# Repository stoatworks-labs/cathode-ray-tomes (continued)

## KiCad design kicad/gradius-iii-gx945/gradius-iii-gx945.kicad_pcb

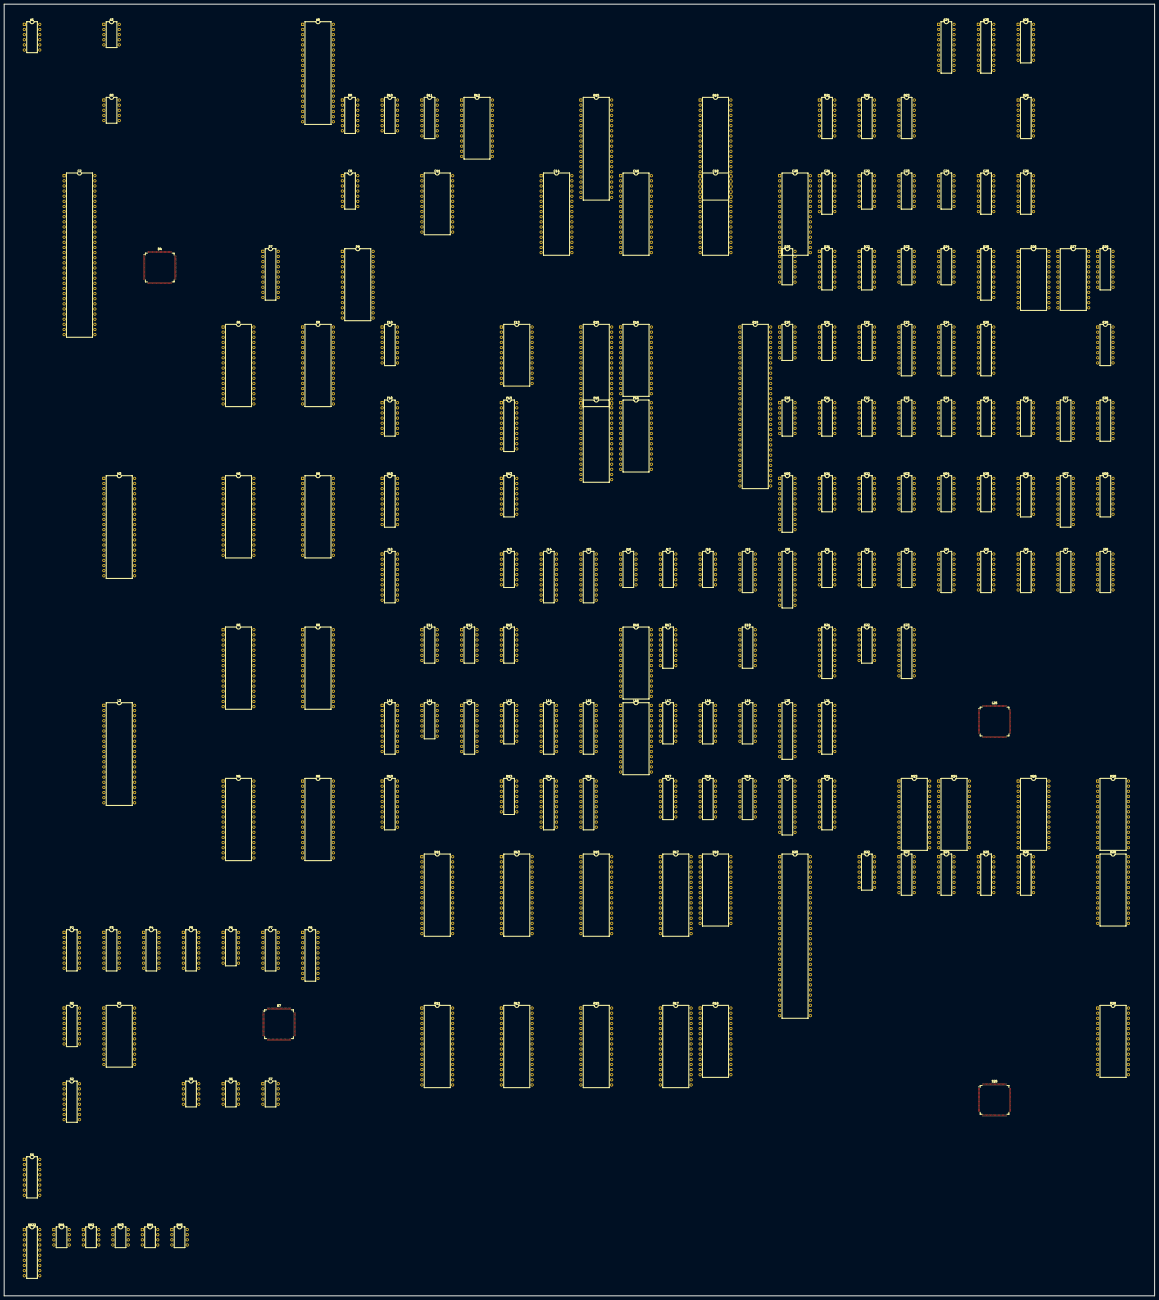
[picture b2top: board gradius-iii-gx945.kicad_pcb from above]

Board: 2 copper layers, 570.1 x 640.1 mm, 180 parts (0 on the bottom side), 849 nets, no tracks yet.

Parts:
A1: MB3731; DIP-12_W7.62mm
A3: 007340; DIP-10_W7.62mm
A8: Z80; DIP-40_W15.24mm
A24: 74LS244; DIP-20_W7.62mm
A25: 74LS273; DIP-20_W7.62mm
A26: 74LS257; DIP-16_W7.62mm
B3: 007340; DIP-10_W7.62mm
B9: 74LS04; DIP-14_W7.62mm
B10: UPC324; DIP-14_W7.62mm
B11: YM3012; DIP-16_W7.62mm
B12: 051550; DIP-24_W15.24mm
B15, B18: 23C4100; DIP-40_W15.24mm
B21: 74LS157; DIP-16_W7.62mm
B22, B23: 74LS138; DIP-16_W7.62mm
B26: 74LS257; DIP-16_W7.62mm
C2: 007232; DIP-64_W15.24mm
C9: UPC324; DIP-14_W7.62mm
C11: YM2151; DIP-24_W15.24mm
C14, C16, C18, C20: 27C1000; DIP-32_W15.24mm
C21: 74LS174; DIP-16_W7.62mm
C22, C23, C24: 74LS07; DIP-14_W7.62mm
C25, C26: 74LS253; DIP-16_W7.62mm
D4: 051937; TQFP-120_14x14mm_P0.4mm
D7, D25: 74LS273; DIP-20_W7.62mm
D9: 27C512; DIP-28_W15.24mm
D20: 74LS04; DIP-14_W7.62mm
D21: 74LS174; DIP-16_W7.62mm
D22: 74LS139; DIP-16_W7.62mm
D23: 74LS74; DIP-14_W7.62mm
D24: 74LS07; DIP-14_W7.62mm
D26, D27: SRAM2K8B; DIP-24_W15.24mm
D28: 74LS253; DIP-16_W7.62mm
E6, E8: 27C1000; DIP-32_W15.24mm
E10: 74LS138; DIP-16_W7.62mm
E13: SRAM2K8B; DIP-24_W15.24mm
E15: 27C1000-255; DIP-32_W15.24mm
E16: SRAM8K8B; DIP-28_W15.24mm
E19: MC68000; DIP-64_W15.24mm
E20: 74LS32; DIP-14_W7.62mm
E21: 74LS04; DIP-14_W7.62mm
E22: 74LS74; DIP-14_W7.62mm
E23, E24: 74LS245; DIP-20_W7.62mm
E25: 74LS273; DIP-20_W7.62mm
E28: 74LS253; DIP-16_W7.62mm
F10: 74LS08; DIP-14_W7.62mm
F13: 74LS374; DIP-20_W7.62mm
F15: 27C1000-255; DIP-32_W15.24mm
F16: SRAM8K8B; DIP-28_W15.24mm
F20, F23, F26: 74LS32; DIP-14_W7.62mm
F21: 74LS04; DIP-14_W7.62mm
F22, F24: 74LS74; DIP-14_W7.62mm
F25: 74LS07; DIP-14_W7.62mm
F27, F28: 74LS157; DIP-16_W7.62mm
H3: 23C4100; DIP-40_W15.24mm
H6, H8: 27C1000; DIP-32_W15.24mm
H10: 74LS244; DIP-20_W7.62mm
H13: 74LS139; DIP-16_W7.62mm
H20: 007644; DIP-22_W7.62mm
H21: 74LS74; DIP-14_W7.62mm
H22: 74LS08; DIP-14_W7.62mm
H23: 74LS10; DIP-14_W7.62mm
H24: 74LS32; DIP-14_W7.62mm
H25: 74LS04; DIP-14_W7.62mm
H26: 74LS174; DIP-16_W7.62mm
H27: 74LS273; DIP-20_W7.62mm
H28: 74LS157; DIP-16_W7.62mm
J10, J14, J15: 74LS244; DIP-20_W7.62mm
J13: 74LS08; DIP-14_W7.62mm
J16: 74LS00; DIP-14_W7.62mm
J17: 74LS32; DIP-14_W7.62mm
J18, J21, J22: 74LS74; DIP-14_W7.62mm
J19: 74LS157; DIP-16_W7.62mm
J20: 007644; DIP-22_W7.62mm
J23: 74LS02; DIP-14_W7.62mm
J24, J25, J26, J27: 74LS153; DIP-16_W7.62mm
J28: PROM256W4B; DIP-16_W7.62mm
K6, K8: 27C1000; DIP-32_W15.24mm
K11: 74LS04; DIP-14_W7.62mm
K12: 74LS74; DIP-14_W7.62mm
K13: 74LS08; DIP-14_W7.62mm
K16: SRAM8K8B; DIP-28_W15.24mm
K17, K19: 74LS157; DIP-16_W7.62mm
K21: 74LS245; DIP-20_W7.62mm
K22: 74LS07; DIP-14_W7.62mm
K23: 74LS244; DIP-20_W7.62mm
KK22: 74LS245; DIP-20_W7.62mm
L3: 23C4100; DIP-40_W15.24mm
L10, L12: 74LS244; DIP-20_W7.62mm
L11: 74LS74; DIP-14_W7.62mm
L13: 74LS138; DIP-16_W7.62mm
L14, L15, L21: 74LS245; DIP-20_W7.62mm
L16: SRAM8K8B; DIP-28_W15.24mm
L17, L18, L19: 74LS157; DIP-16_W7.62mm
L20: 007644; DIP-22_W7.62mm
L25: 051962; TQFP-120_14x14mm_P0.4mm
M6, M8: 27C1000; DIP-32_W15.24mm
M10: 74LS244; DIP-20_W7.62mm
M13: 74LS04; DIP-14_W7.62mm
M14, M15, M21: 74LS245; DIP-20_W7.62mm
M17, M18, M19: 74LS157; DIP-16_W7.62mm
M20: 007644; DIP-22_W7.62mm
M23, M24, M26, M28: SRAM32K8B; DIP-28_W15.24mm
N11, N13, N15, N17: 27C1000-255; DIP-32_W15.24mm
N18, N28: SRAM8K8B; DIP-28_W15.24mm
N20: MC68000; DIP-64_W15.24mm
N22: 74LS00; DIP-14_W7.62mm
N23, N24, N25, N26: 74LS157; DIP-16_W7.62mm
P2, P3, P4, P5, P7: 74LS157; DIP-16_W7.62mm
P6: 74LS32; DIP-14_W7.62mm
P8: 74LS244; DIP-20_W7.62mm
R2: 74LS174; DIP-16_W7.62mm
R3: SRAM2K8B; DIP-24_W15.24mm
R7: 051960; TQFP-120_14x14mm_P0.4mm
R11, R13, R15, R17: 27C1000-255; DIP-32_W15.24mm
R18, R28: SRAM8K8B; DIP-28_W15.24mm
RN1, RN2, RN3, RN4, RN5: 005273; DIP-8_W7.62mm
S2: 74LS367; DIP-16_W7.62mm
S5, S6, S7: 052535; DIP-10_W7.62mm
S25: 052109; TQFP-120_14x14mm_P0.4mm
U1: 74LS157; DIP-16_W7.62mm

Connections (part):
+12V: A1.11, B10.4, B12.19, C9.4
/10M: E19.15, J14.3
/10M': J14.7, J21.3, J21.11
/10M'': J14.12, N20.15
/CLK24M: D4.2, M13.10, R7.2
/CLK24M': L25.90, M13.8, S25.65
/CLK24M'': J18.3, M13.2
/CLK24M''': E21.5, F22.11, F24.3, H25.13, M13.4
/CPU Master/COIN1: B12.15, E25.2
/CPU Master/COIN2: B12.16, E25.5
/CPU Master/MA1: A24.2, E15.12, E16.10, E19.29, F15.12, F16.10, L17.2
/CPU Master/MA2: A24.4, E15.11, E16.9, E19.30, F15.11, F16.9, L17.5
/CPU Master/MA3: A24.6, E15.10, E16.8, E19.31, F15.10, F16.8, L17.11
/CPU Master/MA4: A24.8, E15.9, E16.7, E19.32, F15.9, F16.7, L17.14
/CPU Master/MA5: A24.11, E15.8, E16.6, E19.33, F15.8, F16.6, M17.2
/CPU Master/MA6: A24.13, E15.7, E16.5, E19.34, F15.7, F16.5, M17.5
/CPU Master/MA7: A24.15, E15.6, E16.4, E19.35, F15.6, F16.4, M17.11
/CPU Master/MA8: A24.17, E15.5, E16.3, E19.36, F15.5, F16.3, M17.14
/CPU Master/MA9: E15.27, E16.25, E19.37, F15.27, F16.25, K17.2, K23.2
/CPU Master/MA10: E15.26, E16.24, E19.38, F15.26, F16.24, K17.5, K23.4
/CPU Master/MA11: E15.23, E16.21, E19.39, F15.23, F16.21, K17.11, K23.6
/CPU Master/MA12: E15.25, E16.23, E19.40, F15.25, F16.23, K17.14, K23.8
/CPU Master/MA13: E15.4, E16.2, E19.41, F15.4, F16.2, J19.2, K23.11
/CPU Master/MA14: E15.28, E19.42, F15.28, K23.13
/CPU Master/MA15: B22.1, E15.29, E19.43, F15.29, K23.15
/CPU Master/MA16: B22.2, E15.3, E19.44, F15.3, K23.17
/CPU Master/MA17: B22.3, E15.2, E19.45, F15.2
/CPU Master/MA18: B23.1, E19.46
/CPU Master/MA19: B23.2, E19.47
/CPU Master/MA20: B23.3, E19.48, F23.2
/CPU Master/MA23: B23.4, E19.52, J16.1
/CPU Master/MAS: E21.12, H22.9, J16.2
/CPU Master/MD0: E19.5, F15.13, F16.11, L15.18
/CPU Master/MD1: E19.4, F15.14, F16.12, L15.17
/CPU Master/MD2: E19.3, F15.15, F16.13, L15.16
/CPU Master/MD3: E19.2, F15.17, F16.15, L15.15
/CPU Master/MD4: E19.1, F15.18, F16.16, L15.14
/CPU Master/MD5: E19.64, F15.19, F16.17, L15.13
/CPU Master/MD6: E19.63, F15.20, F16.18, L15.12
/CPU Master/MD7: E19.62, F15.21, F16.19, L15.11
/CPU Master/MD8: E15.13, E16.11, E19.61, E25.3, M15.18
/CPU Master/MD9: E15.14, E16.12, E19.60, E25.4, M15.17
/CPU Master/MD10: E15.15, E16.13, E19.59, E25.7, M15.16
/CPU Master/MD11: E15.17, E16.15, E19.58, E25.8, M15.15
/CPU Master/MD12: E15.18, E16.16, E19.57, E25.13, M15.14
/CPU Master/MD13: E15.19, E16.17, E19.56, E25.14, M15.13
/CPU Master/MD14: E15.20, E16.18, E19.55, E25.17, M15.12
/CPU Master/MD15: E15.21, E16.19, E19.54, E25.18, M15.11
/CPU Master/MIRQEN: E25.16, H21.4
/CPU Master/MR~W: D20.5, E19.9, E20.4, E20.13, J15.2
/CPU Master/MR~W': F23.5, J15.18, L15.1, M15.1
/CPU Master/MVBIRQEN0: E25.12, J22.4
/CPU Master/MVBIRQEN1: E25.15, H21.10
/CPU Master/M~RW: D20.6, E16.22, F16.22, F26.9, U1.10
/CPU Master/PRIO: E25.6, J28.15
/CPU Master/~AFR: B12.1, B22.11
/CPU Master/~CABINPUTS: B22.14, C25.1, C25.15, C26.1, C26.15, D28.1, D28.15, E28.1, E28.15
/CPU Master/~DIPSW: A26.15, B22.13, B26.15
/CPU Master/~MAS: B23.5, E19.6, E21.13, J15.4
/CPU Master/~MCHRAMW: B23.9, F20.12, H22.1
/CPU Master/~MDTACK: D24.8, D24.10, D24.12, E19.10
/CPU Master/~MHALT: E19.17, F25.8
/CPU Master/~MLDS: E19.8, E20.12
/CPU Master/~MLWR: E20.11, F16.27, F26.2, F26.5, U1.3
/CPU Master/~MRAM: B23.14, E16.20, F16.20
/CPU Master/~MRESET: E19.18, F25.10
/CPU Master/~MROM: B23.15, E15.24, F15.24
/CPU Master/~MUDS: E19.7, E20.5
/CPU Master/~MUWR: E16.27, E20.1, E20.6, F26.12, U1.6
/CPU Master/~PALRAM: E21.4, E23.19, E24.19, F26.1, F26.13, F27.1, F28.1, H28.1
/CPU Master/~SCPURST: D24.3, E25.9, F25.5, K13.2, R2.1
/CPU Master/~SIRQ: B22.12, J22.11
/CPU Master/~SNDDATA: B22.10, F13.11
/CPU Master/~SNDIRQ: B22.9, E22.11
/CPU Master/~VBLK: J22.3, K11.1, K11.3, R7.3
/CPU Slave/SA1: L12.2, L17.3, N11.12, N13.12, N15.12, N17.12, N18.10, N20.29, R11.12, R13.12, R15.12, R17.12, R18.10
/CPU Slave/SA2: L12.4, L17.6, N11.11, N13.11, N15.11, N17.11, N18.9, N20.30, R11.11, R13.11, R15.11, R17.11, R18.9
/CPU Slave/SA3: L12.6, L17.10, N11.10, N13.10, N15.10, N17.10, N18.8, N20.31, R11.10, R13.10, R15.10, R17.10, R18.8
/CPU Slave/SA4: L12.8, L17.13, N11.9, N13.9, N15.9, N17.9, N18.7, N20.32, R11.9, R13.9, R15.9, R17.9, R18.7
/CPU Slave/SA5: L12.11, M17.3, N11.8, N13.8, N15.8, N17.8, N18.6, N20.33, R11.8, R13.8, R15.8, R17.8, R18.6
/CPU Slave/SA6: L12.13, M17.6, N11.7, N13.7, N15.7, N17.7, N18.5, N20.34, R11.7, R13.7, R15.7, R17.7, R18.5
/CPU Slave/SA7: L12.15, M17.10, N11.6, N13.6, N15.6, N17.6, N18.4, N20.35, R11.6, R13.6, R15.6, R17.6, R18.4
/CPU Slave/SA8: L12.17, M17.13, N11.5, N13.5, N15.5, N17.5, N18.3, N20.36, R11.5, R13.5, R15.5, R17.5, R18.3
/CPU Slave/SA9: K17.3, N11.27, N13.27, N15.27, N17.27, N18.25, N20.37, P8.2, R11.27, R13.27, R15.27, R17.27, R18.25
/CPU Slave/SA10: K17.6, N11.26, N13.26, N15.26, N17.26, N18.24, N20.38, P8.4, R11.26, R13.26, R15.26, R17.26, R18.24
/CPU Slave/SA11: K17.10, N11.23, N13.23, N15.23, N17.23, N18.21, N20.39, P8.6, R11.23, R13.23, R15.23, R17.23, R18.21
/CPU Slave/SA12: K17.13, N11.25, N13.25, N15.25, N17.25, N18.23, N20.40, P8.8, R11.25, R13.25, R15.25, R17.25, R18.23
/CPU Slave/SA13: J19.3, N11.4, N13.4, N15.4, N17.4, N18.2, N20.41, P8.11, R11.4, R13.4, R15.4, R17.4, R18.2
/CPU Slave/SA14: N11.28, N13.28, N15.28, N17.28, N20.42, P8.13, R11.28, R13.28, R15.28, R17.28
/CPU Slave/SA15: N11.29, N13.29, N15.29, N17.29, N20.43, P8.15, R11.29, R13.29, R15.29, R17.29
/CPU Slave/SA16: N11.3, N13.3, N15.3, N17.3, N20.44, P8.17, R11.3, R13.3, R15.3, R17.3
/CPU Slave/SA17: N11.2, N13.2, N15.2, N17.2, N20.45, R11.2, R13.2, R15.2, R17.2, S2.2
/CPU Slave/SA18: H13.2, L13.1, N20.46, S2.4
/CPU Slave/SA19: H13.3, L13.2, N20.47, S2.6
/CPU Slave/SA20: L13.3, N20.48, S2.10
/CPU Slave/SA21: E21.11, F20.1, L13.4, N20.50
/CPU Slave/SA22: F21.13, F23.12, L13.5, N20.51
/CPU Slave/SA23: J16.5, N20.52
/CPU Slave/SAS: J16.4, J21.4, J21.10, K11.6, K12.4, K13.1, L13.6
/CPU Slave/SIRQEN: J22.10, R2.7
/CPU Slave/SR~W: F21.11, H24.9, H24.12, J14.6, N20.9
/CPU Slave/SVBIRQEN0: L11.4, R2.2
/CPU Slave/SVBIRQEN1: L11.10, R2.5
/CPU Slave/S~RW: D4.7, F20.10, F21.10, N18.22, R7.12, R18.22, U1.11
/CPU Slave/~MIRQ: H21.3, K22.13, L13.9
/CPU Slave/~OBJCS: D4.8, K12.5, K22.11, R7.13
/CPU Slave/~OBJROMRD: F20.6, J13.10, P2.1, P3.1, P4.1, P5.1, P6.1, P6.4, P6.9, P6.12, P7.1
/CPU Slave/~SAS': J14.9, K11.5
/CPU Slave/~SAS: F20.5, H24.2, J14.11, N20.6
/CPU Slave/~SCHRAMW: H13.6, J13.1, J17.1
/CPU Slave/~SDTACK: F25.2, F25.12, K22.2, K22.4, K22.6, K22.8, K22.10, K22.12, N20.10
/CPU Slave/~SHALT: F25.6, N20.17
/CPU Slave/~SIRQEN: K22.3, L13.10, R2.9
/CPU Slave/~SLDS: H24.13, N20.8
/CPU Slave/~SLWR: H24.11, J17.4, N18.27, U1.2
/CPU Slave/~SRAM: K22.5, L13.11, N18.20, R18.20
/CPU Slave/~SRESET: D24.4, N20.18
/CPU Slave/~SROM0: K22.9, L13.15, N17.24, R17.24
/CPU Slave/~SROM1: K13.13, L13.14, N15.24, R15.24
/CPU Slave/~SROM2: K13.9, L13.13, N11.24, R11.24
/CPU Slave/~SROM3: K13.10, L13.12, N13.24, R13.24
/CPU Slave/~SUDS: H24.10, N20.7
/CPU Slave/~SUWR: E20.9, H24.8, R18.27, U1.5
/CPU Slave/~VBLK: D4.29, K11.11, L11.3
/Color Mixer/B0: A25.3, D27.9, E24.18
/Color Mixer/B1: A25.4, D27.10, E24.17
/Color Mixer/B2: A25.7, D27.11, E24.16
/Color Mixer/B3: A25.8, D27.13, E24.15
/Color Mixer/B4: A25.13, D27.14, E24.14
/Color Mixer/B'0: A25.2, D24.5
/Color Mixer/B'1: A25.5, C23.11
/Color Mixer/B'2: A25.6, C24.9
/Color Mixer/B'3: A25.9, F25.3
/Color Mixer/B'4: A25.12, C23.3
/Color Mixer/CD0: H27.3, J25.7
/Color Mixer/CD1: H27.4, J25.9
/Color Mixer/CD2: H27.7, J27.7
/Color Mixer/CD3: H27.8, J27.9
/Color Mixer/CD4: H27.13, J26.7
/Color Mixer/CD5: H27.14, J26.9
/Color Mixer/CD6: H27.17, J24.7
/Color Mixer/CD7: H27.18, J24.9
/Color Mixer/CD8: H26.3, J24.14, J25.14, J26.14, J27.14, J28.12
/Color Mixer/CD9: H26.4, J24.2, J25.2, J26.2, J27.2, J28.11
/Color Mixer/CD'0: F28.3, H27.2
/Color Mixer/CD'1: F28.6, H27.5
/Color Mixer/CD'2: F28.10, H27.6
/Color Mixer/CD'3: F28.13, H27.9
/Color Mixer/CD'4: F27.3, H27.12
/Color Mixer/CD'5: F27.6, H27.15
/Color Mixer/CD'6: F27.10, H27.16
/Color Mixer/CD'7: F27.13, H27.19
/Color Mixer/CD'8: H26.2, H28.3
/Color Mixer/CD'9: H26.5, H28.6
/Color Mixer/CD''0: D26.4, D27.2, F28.4
/Color Mixer/CD''1: D26.2, D27.23, F28.7
/Color Mixer/CD''2: D26.1, D27.1, F28.9
/Color Mixer/CD''3: D26.8, D27.5, F28.12
/Color Mixer/CD''4: D26.7, D27.4, F27.4
/Color Mixer/CD''5: D26.5, D27.3, F27.7
/Color Mixer/CD''6: D26.22, D27.7, F27.9
/Color Mixer/CD''7: D26.23, D27.8, F27.12
/Color Mixer/CD''8: D26.3, D27.22, H28.4
/Color Mixer/CD''9: D26.6, D27.19, H28.7
/Color Mixer/CD''10: D26.19, D27.6, H28.9
/Color Mixer/CLK6M: A25.11, D4.116, D25.11, H26.9, H27.11
/Color Mixer/FX0: J25.6, L25.59
/Color Mixer/FX1: J25.10, L25.60
/Color Mixer/FX2: J27.6, L25.62
/Color Mixer/FX3: J27.10, L25.63
/Color Mixer/FX4: J26.6, L25.64
/Color Mixer/FX5: J26.10, L25.65
/Color Mixer/FX6: J24.6, L25.66
/Color Mixer/G0: A25.14, D27.15, E24.13
/Color Mixer/G1: A25.17, D27.16, E24.12
/Color Mixer/G2: A25.18, D27.17, E24.11
/Color Mixer/G3: D25.3, D26.9, E23.18
/Color Mixer/G4: D25.4, D26.10, E23.17
/Color Mixer/G'0: A25.15, C23.1
/Color Mixer/G'1: A25.16, C23.5
/Color Mixer/G'2: A25.19, C24.5
/Color Mixer/G'3: C23.13, D25.2
/Color Mixer/G'4: C24.13, D25.5
/Color Mixer/OB0: D4.35, J27.11
/Color Mixer/OB1: D4.36, J27.5
/Color Mixer/OB2: D4.37, J25.11
/Color Mixer/OB3: D4.38, J25.5
/Color Mixer/OB5: D4.40, J26.5
/Color Mixer/OB6: D4.41, J26.11
/Color Mixer/OB7: D4.42, J24.5
/Color Mixer/OB8: D4.43, J24.11
/Color Mixer/OB9: D4.46, J28.3
/Color Mixer/OB10: D4.47, J28.2
/Color Mixer/PAL: D26.17, E23.11
/Color Mixer/R0: D25.7, D26.11, E23.16
/Color Mixer/R1: D25.8, D26.13, E23.15
/Color Mixer/R2: D25.13, D26.14, E23.14
/Color Mixer/R3: D25.14, D26.15, E23.13
/Color Mixer/R4: D25.17, D26.16, E23.12
/Color Mixer/R'0: C24.3, D25.6
/Color Mixer/R'1: C24.11, D25.9
/Color Mixer/R'2: C24.1, D25.12
/Color Mixer/R'3: C23.9, D25.15
/Color Mixer/R'4: D24.1, D25.16
/Color Mixer/SHADOW': D4.32, J28.1
/Color Mixer/VA0: J25.4, L25.46
/Color Mixer/VA1: J25.12, L25.47
/Color Mixer/VA2: J27.4, L25.48
/Color Mixer/VA3: J27.12, L25.49
/Color Mixer/VA4: J26.4, L25.50
/Color Mixer/VA5: J26.12, L25.51
/Color Mixer/VA6: J24.4, L25.52
/Color Mixer/VB0: J25.3, L25.30
/Color Mixer/VB1: J25.13, L25.32
/Color Mixer/VB2: J27.3, L25.33
/Color Mixer/VB3: J27.13, L25.34
/Color Mixer/VB4: J26.3, L25.35
/Color Mixer/VB5: J26.13, L25.36
/Color Mixer/VB6: J24.3, L25.37
/Color Mixer/~CBLK'': C22.9, C22.11, C22.13, D25.19
/Color Mixer/~CBLK': D25.18, H26.15
/Color Mixer/~CBLK: D4.28, H26.14
/Color Mixer/~CDEN': H26.7, H28.10
/Color Mixer/~CDEN: H26.6, J24.1, J24.15, J25.1, J25.15, J26.1, J26.15, J27.1, J27.15, J28.9
/Color Mixer/~FX: J28.5, L25.68
/Color Mixer/~OBJ: D4.33, J28.6
/Color Mixer/~PALOE: D26.20, D27.20, H28.12
/Color Mixer/~SHADOW': C22.1, C22.3, C22.5, H26.12
/Color Mixer/~SHADOW: H26.11, J28.10
/Color Mixer/~VA: J28.7, L25.58
/Color Mixer/~VB: J28.4, L25.43
/IO/INPUT0: D28.5, RN1.7
/IO/INPUT1: E28.13, RN1.5
/IO/INPUT2: E28.12, RN1.3
/IO/INPUT3: E28.11, RN1.1
/IO/INPUT4: D28.12, RN2.7
/IO/INPUT5: D28.11, RN2.5
/IO/INPUT7: D28.4, RN2.1
/IO/INPUT8: C25.4, RN3.7
/IO/INPUT9: C25.5, RN3.5
/IO/INPUT10: C26.12, RN3.3
/IO/INPUT11: C26.11, RN3.1
/IO/INPUT12: C26.3, RN4.7
/IO/INPUT13: C26.4, RN4.5
/IO/INPUT14: C26.5, RN4.3
/IO/INPUT15: D28.13, RN4.1
/IO/INPUT16: C25.13, RN5.7
/IO/INPUT17: C25.12, RN5.5
/IO/INPUT18: C25.11, RN5.3
/IO/INPUT19: C25.3, RN5.1
/IO/~COINCOUNTER1: B12.22, B12.23
/IO/~COINCOUNTER2: B12.20, B12.21
/MBA1: A24.18, A26.1, B26.1, F28.2, H25.1, K19.3
/MBA2: A24.16, F28.5, H25.3, K19.6
/MBA3: A24.14, F28.11, K19.10
/MBA4: A24.12, F28.14, K19.13
/MBA5: A24.9, F27.2, M19.3
/MBA6: A24.7, F27.5, M19.6
/MBA7: A24.5, F27.11, M19.10
/MBA8: A24.3, F27.14, M19.13
/MBA9: H28.2, K23.18, M18.3
/MBA10: H28.5, K23.16, M18.6
/MBA11: H28.11, K23.14, M18.10
/MBA12: K23.12, M18.13
/MBA13: K23.9, L19.3
/MBA14: K23.7, L19.6
/MBA15: K23.5, L19.10
/MBA16: K23.3, L19.13
/MD0: A26.4, C25.9, E24.2, L20.13
/MD1: A26.7, C25.7, E24.3, L20.14
/MD2: A26.9, C26.9, E24.4, L20.15
/MD3: A26.12, C26.7, E24.5, L20.16
/MD4: B26.4, D28.9, E24.6, L20.17
/MD5: B26.7, D28.7, E24.7, L20.18
/MD6: B26.9, E24.8, E28.9, L20.19
/MD7: B26.12, E24.9, E28.7, L20.20
/MD8: E23.2, F13.3, H20.13
/MD9: E23.3, F13.4, H20.14
/MD10: E23.4, F13.7, H20.15
/MD11: E23.5, F13.8, H20.16
/MD12: E23.6, F13.13, H20.17
/MD13: E23.7, F13.14, H20.18
/MD14: E23.8, F13.17, H20.19
/MD15: E23.9, F13.18, H20.20
/Misc/SR~W': J14.14, J17.9, L14.1, M14.1
/Misc/~CSYNC: D4.25, J14.2
/Misc/~RESET': J14.5, J18.1, J18.2
/Misc/~RESET: B12.10, J14.15
/Misc/~VSYNC: D4.26, J14.4
/Object Layer/A0: E6.12, E8.12, H3.9, H6.12, H8.12, K6.12, K8.12, L3.9, M6.12, M8.12, P7.4
/Object Layer/A1: E6.11, E8.11, H3.8, H6.11, H8.11, K6.11, K8.11, L3.8, M6.11, M8.11, P7.7
/Object Layer/A2: E6.10, E8.10, H3.7, H6.10, H8.10, K6.10, K8.10, L3.7, M6.10, M8.10, P7.9
/Object Layer/A3: E6.9, E8.9, H3.6, H6.9, H8.9, K6.9, K8.9, L3.6, M6.9, M8.9, P7.12
/Object Layer/A4: E6.8, E8.8, H3.5, H6.8, H8.8, K6.8, K8.8, L3.5, M6.8, M8.8, P5.4
/Object Layer/A5: E6.7, E8.7, H3.4, H6.7, H8.7, K6.7, K8.7, L3.4, M6.7, M8.7, P5.7
/Object Layer/A6: E6.6, E8.6, H3.3, H6.6, H8.6, K6.6, K8.6, L3.3, M6.6, M8.6, P5.9
/Object Layer/A7: E6.5, E8.5, H3.2, H6.5, H8.5, K6.5, K8.5, L3.2, M6.5, M8.5, P5.12
/Object Layer/A8: E6.27, E8.27, H3.40, H6.27, H8.27, K6.27, K8.27, L3.40, M6.27, M8.27, P4.4
/Object Layer/A9: E6.26, E8.26, H3.39, H6.26, H8.26, K6.26, K8.26, L3.39, M6.26, M8.26, P4.7
/Object Layer/A10: E6.23, E8.23, H3.38, H6.23, H8.23, K6.23, K8.23, L3.38, M6.23, M8.23, P4.9
/Object Layer/A11: E6.25, E8.25, H3.37, H6.25, H8.25, K6.25, K8.25, L3.37, M6.25, M8.25, P4.12
/Object Layer/A12: E6.4, E8.4, H3.36, H6.4, H8.4, K6.4, K8.4, L3.36, M6.4, M8.4, P3.4
/Object Layer/A13: E6.28, E8.28, H3.35, H6.28, H8.28, K6.28, K8.28, L3.35, M6.28, M8.28, P3.7
/Object Layer/A14: E6.29, E8.29, H3.34, H6.29, H8.29, K6.29, K8.29, L3.34, M6.29, M8.29, P3.9
/Object Layer/A15: E6.3, E8.3, H3.33, H6.3, H8.3, K6.3, K8.3, L3.33, M6.3, M8.3, P3.12
/Object Layer/A16: E6.2, E8.2, H3.32, H6.2, H8.2, K6.2, K8.2, L3.32, M6.2, M8.2, P2.4
/Object Layer/A17: H3.1, H13.14, L3.1, P2.7
/Object Layer/A18: H13.13, P2.9
/Object Layer/CA0: P7.3, R7.68
/Object Layer/CA1: P7.6, R7.69
/Object Layer/CA2: P7.10, R7.70
/Object Layer/CA3: P7.13, R7.71
/Object Layer/CA4: P5.3, R7.72
/Object Layer/CA5: P5.6, R7.73
/Object Layer/CA6: P5.10, R7.76
/Object Layer/CA7: P5.13, R7.77
/Object Layer/CA8: P4.3, R7.78
/Object Layer/CA9: P4.6, R7.79
/Object Layer/CA10: P4.10, R7.80
/Object Layer/CA11: P4.13, R7.81
/Object Layer/CA12: P3.3, R7.82
/Object Layer/CA13: P3.6, R7.84
/Object Layer/CA14: P3.10, R7.85
/Object Layer/CA15: P3.13, R7.86
/Object Layer/CA16: P2.3, R7.87
/Object Layer/CA17: P2.6, R7.88
/Object Layer/CARY: D4.111, R7.43
/Object Layer/CD0: D4.49, E6.13, E8.13, H3.13, H10.2
/Object Layer/CD1: D4.50, E6.18, E8.18, H3.22, H10.11
/Object Layer/CD2: D4.51, H3.14, H6.13, H8.13, J10.2
/Object Layer/CD3: D4.52, H3.23, H6.18, H8.18, J10.11
/Object Layer/CD4: D4.53, K6.13, K8.13, L3.13, L10.2
/Object Layer/CD5: D4.54, K6.18, K8.18, L3.22, L10.11
/Object Layer/CD6: D4.55, L3.14, M6.13, M8.13, M10.2
/Object Layer/CD7: D4.56, L3.23, M6.18, M8.18, M10.11
/Object Layer/CD10: D4.57, E6.14, E8.14, H3.15, H10.4
/Object Layer/CD11: D4.58, E6.19, E8.19, H3.24, H10.13
/Object Layer/CD12: D4.59, H3.16, H6.14, H8.14, J10.4
/Object Layer/CD13: D4.62, H3.25, H6.19, H8.19, J10.13
/Object Layer/CD14: D4.63, K6.14, K8.14, L3.15, L10.4
/Object Layer/CD15: D4.64, K6.19, K8.19, L3.24, L10.13
/Object Layer/CD16: D4.65, L3.16, M6.14, M8.14, M10.4
/Object Layer/CD17: D4.66, L3.25, M6.19, M8.19, M10.13
/Object Layer/CD20: D4.67, E6.15, E8.15, H3.17, H10.6
/Object Layer/CD21: D4.68, E6.20, E8.20, H3.26, H10.15
/Object Layer/CD22: D4.69, H3.18, H6.15, H8.15, J10.6
/Object Layer/CD23: D4.70, H3.27, H6.20, H8.20, J10.15
/Object Layer/CD24: D4.71, K6.15, K8.15, L3.17, L10.6
/Object Layer/CD25: D4.72, K6.20, K8.20, L3.26, L10.15
/Object Layer/CD26: D4.73, L3.18, M6.15, M8.15, M10.6
/Object Layer/CD27: D4.76, L3.27, M6.20, M8.20, M10.15
/Object Layer/CD30: D4.77, E6.17, E8.17, H3.19, H10.8
/Object Layer/CD31: D4.78, E6.21, E8.21, H3.28, H10.17
/Object Layer/CD32: D4.79, H3.20, H6.17, H8.17, J10.8
/Object Layer/CD33: D4.80, H3.29, H6.21, H8.21, J10.17
/Object Layer/CD34: D4.81, K6.17, K8.17, L3.19, L10.8
/Object Layer/CD35: D4.82, K6.21, K8.21, L3.28, L10.17
/Object Layer/CD36: D4.84, L3.20, M6.17, M8.17, M10.8
/Object Layer/CD37: D4.85, L3.29, M6.21, M8.21, M10.17
/Object Layer/HEND: D4.113, R7.41
/Object Layer/HP0: D4.110, R7.46
/Object Layer/HP1: D4.109, R7.47
/Object Layer/HP2: D4.108, R7.48
/Object Layer/HP3: D4.107, R7.49
/Object Layer/HP4: D4.106, R7.50
/Object Layer/HP5: D4.103, R7.51
/Object Layer/HP6: D4.102, R7.52
/Object Layer/HP7: D4.101, R7.53
/Object Layer/HP8: D4.100, R7.54
/Object Layer/LACH: D4.112, R7.42
/Object Layer/OA0: R3.8, R7.99
/Object Layer/OA1: R3.7, R7.98
/Object Layer/OA2: R3.6, R7.97
/Object Layer/OA3: R3.5, R7.96
/Object Layer/OA4: R3.4, R7.95
/Object Layer/OA5: R3.3, R7.94
/Object Layer/OA6: R3.2, R7.93
/Object Layer/OA7: R3.1, R7.92
/Object Layer/OA8: R3.23, R7.90
/Object Layer/OA9: R3.22, R7.89
/Object Layer/OC0: P2.10, R7.55
/Object Layer/OC1: D4.98, R7.56
/Object Layer/OC2: D4.97, R7.57
/Object Layer/OC3: D4.96, R7.58
/Object Layer/OC4: D4.95, R7.59
/Object Layer/OC5: D4.94, R7.62
/Object Layer/OC6: D4.93, R7.63
/Object Layer/OC7: D4.92, R7.64
/Object Layer/OD0: R3.9, R7.111
/Object Layer/OD1: R3.10, R7.110
/Object Layer/OD2: R3.11, R7.109
/Object Layer/OD3: R3.13, R7.108
/Object Layer/OD4: R3.14, R7.107
/Object Layer/OD5: R3.15, R7.106
/Object Layer/OD6: R3.16, R7.103
/Object Layer/OD7: R3.17, R7.102
/Object Layer/OHF: D4.115, R7.39
/Object Layer/~HVOT: D4.5, R7.5, S25.99
/Object Layer/~OOE: R3.20, R7.101
/Object Layer/~OREG: D4.114, R7.40
/Object Layer/~ORHRD': M10.1, M10.19, P6.6
/Object Layer/~ORHRD: L10.1, L10.19, P6.3
/Object Layer/~ORLRD': J10.1, J10.19, P6.11
/Object Layer/~ORLRD: H10.1, H10.19, P6.8
/Object Layer/~OROM0: H13.12, J13.5, J13.12
/Object Layer/~OROM1: F10.10, F10.13, H13.11, J13.4, J13.13
/Object Layer/~OROM2: E6.22, E6.24, F10.9, F10.12, H6.22, H6.24, H13.10, K6.22, K6.24, M6.22, M6.24
/Object Layer/~OROM3: E8.22, E8.24, H8.22, H8.24, H13.9, K8.22, K8.24, M8.22, M8.24
/Object Layer/~OROMH: J13.6, L3.12
/Object Layer/~OROML: H3.12, J13.11
/Object Layer/~OWR: R3.21, R7.100
/PCM/AS0: B15.29, B18.29, C2.33, C14.12, C16.12, C18.12, C20.12
/PCM/AS1: B15.9, B18.9, C2.34, C14.11, C16.11, C18.11, C20.11
/PCM/AS2: B15.8, B18.8, C2.36, C14.10, C16.10, C18.10, C20.10
/PCM/AS3: B15.7, B18.7, C2.38, C14.9, C16.9, C18.9, C20.9
/PCM/AS4: B15.6, B18.6, C2.39, C14.8, C16.8, C18.8, C20.8
/PCM/AS5: B15.5, B18.5, C2.41, C14.7, C16.7, C18.7, C20.7
/PCM/AS6: B15.4, B18.4, C2.43, C14.6, C16.6, C18.6, C20.6
/PCM/AS7: B15.3, B18.3, C2.45, C14.5, C16.5, C18.5, C20.5
/PCM/AS8: B15.2, B18.2, C2.44, C14.27, C16.27, C18.27, C20.27
/PCM/AS9: B15.40, B18.40, C2.42, C14.26, C16.26, C18.26, C20.26
/PCM/AS10: B15.39, B18.39, C2.35, C14.23, C16.23, C18.23, C20.23
/PCM/AS11: B15.38, B18.38, C2.40, C14.25, C16.25, C18.25, C20.25
/PCM/AS12: B15.37, B18.37, C2.47, C14.4, C16.4, C18.4, C20.4
/PCM/AS13: B15.36, B18.36, C2.46, C14.28, C16.28, C18.28, C20.28
/PCM/AS14: B15.35, B18.35, C2.49, C14.29, C16.29, C18.29, C20.29
/PCM/AS15: B15.34, B18.34, C2.50, C14.3, C16.3, C18.3, C20.3
/PCM/AS16: B15.33, B18.33, C2.37, C14.2, C16.2, C18.2, C20.2
/PCM/DABNK0: B15.32, B18.32, C21.2, D22.13
/PCM/DABNK1: B15.10, B15.12, C21.5, D20.1, D22.14
/PCM/DS0: B15.13, B18.13, C2.25, C14.13, C16.13, C18.13, C20.13
/PCM/DS1: B15.15, B18.15, C2.27, C14.14, C16.14, C18.14, C20.14
/PCM/DS2: B15.17, B18.17, C2.29, C14.15, C16.15, C18.15, C20.15
/PCM/DS3: B15.19, B18.19, C2.31, C14.17, C16.17, C18.17, C20.17
/PCM/DS4: B15.22, B18.22, C2.30, C14.18, C16.18, C18.18, C20.18
/PCM/DS5: B15.24, B18.24, C2.28, C14.19, C16.19, C18.19, C20.19
/PCM/DS6: B15.26, B18.26, C2.26, C14.20, C16.20, C18.20, C20.20
/PCM/DS7: B15.28, B18.28, C2.24, C14.21, C16.21, C18.21, C20.21
/PCM/REF4V: C9.10, C9.12
/PCM/SNDA0: A8.30, B9.9, C11.4, D9.10, E13.8
/PCM/SNDA1: A8.31, C2.59, D9.9, E13.7
/PCM/SNDA2: A8.32, C2.60, D9.8, E13.6
/PCM/SNDA3: A8.33, C2.61, D9.7, E13.5
/PCM/SNDCLK2: B9.6, C21.9, D23.3
/PCM/SNDCLK4: B21.1, D23.2, D23.6
/PCM/SNDD0: A8.14, C2.8, C11.10, D7.3, D9.11, D21.3, E13.9, F13.2
/PCM/SNDD1: A8.15, C2.7, C11.12, D7.4, D9.12, D21.4, E13.10, F13.5
/PCM/SNDD2: A8.12, C2.6, C11.13, D7.7, D9.13, D21.6, E13.11, F13.6
/PCM/SNDD3: A8.8, C2.5, C11.14, D7.8, D9.15, D21.11, E13.13, F13.9
/PCM/SNDD4: A8.7, C2.4, C11.15, D7.13, D9.16, D21.13, E13.14, F13.12
/PCM/SNDD5: A8.9, C2.3, C11.16, D7.14, D9.17, D21.14, E13.15, F13.15
/PCM/SNDD6: A8.10, C2.2, C11.17, D7.17, D9.18, E13.16, F13.16
/PCM/SNDD7: A8.13, C2.1, C11.18, D7.18, D9.19, E13.17, F13.19
/PCM/~BANKSW: D21.9, D22.4
/PCM/~DABNK1: B18.10, B18.12, D20.2
/PCM/~DABNKA0: C14.22, C14.24, D22.12
/PCM/~DABNKA1: C16.22, C16.24, D22.11
/PCM/~DABNKB0: C18.22, C18.24, D22.10
/PCM/~DABNKB1: C20.22, C20.24, D22.9
/PCM/~DACS: C2.62, D22.6
/SBA1: D4.13, K11.9, K19.2, L12.18, P6.2, P6.5, R7.27
/SBA2: D4.12, K19.5, L12.16, P7.2, R7.26
/SBA3: D4.11, K19.11, L12.14, P7.5, R7.25
/SBA4: K19.14, L12.12, P7.11, R7.24
/SBA5: L12.9, M19.2, P7.14, R7.22
/SBA6: L12.7, M19.5, P5.2, R7.21
/SBA7: L12.5, M19.11, P5.5, R7.20
/SBA8: L12.3, M19.14, P5.11, R7.19
/SBA9: M18.2, P5.14, P8.18, R7.18
/SBA10: M18.5, P4.2, P8.16, R7.17
/SBA11: D4.10, M18.11, P4.5, P8.14, R7.16
/SBA12: M18.14, P4.11, P8.12
/SBA13: L19.2, P4.14, P8.9
/SBA14: L19.5, P3.2, P8.7
/SBA15: L19.11, P3.5, P8.5
/SBA16: L19.14, P3.11, P8.3
/SBA17: P3.14, S2.3
/SBA18: P2.2, S2.5
/SBA19: P2.5, S2.7
/SBA20: P2.11, S2.9
/SD0: D4.24, H10.18, L10.18, L14.18, M20.13, N11.13, N13.13, N15.13, N17.13, N18.11, N20.5, R7.37
/SD1: D4.22, H10.16, L10.16, L14.17, M20.14, N11.14, N13.14, N15.14, N17.14, N18.12, N20.4, R7.36
/SD2: D4.21, H10.14, L10.14, L14.16, M20.15, N11.15, N13.15, N15.15, N17.15, N18.13, N20.3, R7.35
/SD3: D4.20, H10.12, L10.12, L14.15, M20.16, N11.17, N13.17, N15.17, N17.17, N18.15, N20.2, R7.34
/SD4: D4.19, H10.9, L10.9, L14.14, M20.17, N11.18, N13.18, N15.18, N17.18, N18.16, N20.1, R7.33
/SD5: D4.18, H10.7, L10.7, L14.13, M20.18, N11.19, N13.19, N15.19, N17.19, N18.17, N20.64, R7.32
/SD6: D4.17, H10.5, L10.5, L14.12, M20.19, N11.20, N13.20, N15.20, N17.20, N18.18, N20.63, R7.30
/SD7: D4.16, H10.3, L10.3, L14.11, M20.20, N11.21, N13.21, N15.21, N17.21, N18.19, N20.62, R7.29
/SD8: J10.18, J20.13, M10.18, M14.18, N20.61, R2.3, R11.13, R13.13, R15.13, R17.13, R18.11
/SD9: J10.16, J20.14, M10.16, M14.17, N20.60, R2.4, R11.14, R13.14, R15.14, R17.14, R18.12
/SD10: J10.14, J20.15, M10.14, M14.16, N20.59, R2.6, R11.15, R13.15, R15.15, R17.15, R18.13
/SD11: J10.12, J20.16, M10.12, M14.15, N20.58, R2.11, R11.17, R13.17, R15.17, R17.17, R18.15
/SD12: J10.9, J20.17, M10.9, M14.14, N20.57, R2.13, R11.18, R13.18, R15.18, R17.18, R18.16
/SD13: J10.7, J20.18, M10.7, M14.13, N20.56, R2.14, R11.19, R13.19, R15.19, R17.19, R18.17
/SD14: J10.5, J20.19, M10.5, M14.12, N20.55, R11.20, R13.20, R15.20, R17.20, R18.18
/SD15: J10.3, J20.20, M10.3, M14.11, N20.54, R11.21, R13.21, R15.21, R17.21, R18.19
/Shared RAM/A0: K16.10, L16.10, L17.4
/Shared RAM/A1: K16.9, L16.9, L17.7
/Shared RAM/A2: K16.8, L16.8, L17.9
/Shared RAM/A3: K16.7, L16.7, L17.12
/Shared RAM/A4: K16.6, L16.6, M17.4
/Shared RAM/A5: K16.5, L16.5, M17.7
/Shared RAM/A6: K16.4, L16.4, M17.9
/Shared RAM/A7: K16.3, L16.3, M17.12
/Shared RAM/A8: K16.25, K17.4, L16.25
/Shared RAM/A9: K16.24, K17.7, L16.24
/Shared RAM/A10: K16.21, K17.9, L16.21
/Shared RAM/A11: K16.23, K17.12, L16.23
/Shared RAM/A12: J19.4, K16.2, L16.2
/Shared RAM/D0: K16.11, L14.2, L15.2
/Shared RAM/D1: K16.12, L14.3, L15.3
/Shared RAM/D2: K16.13, L14.4, L15.4
/Shared RAM/D3: K16.15, L14.5, L15.5
/Shared RAM/D4: K16.16, L14.6, L15.6
/Shared RAM/D5: K16.17, L14.7, L15.7
/Shared RAM/D6: K16.18, L14.8, L15.8
/Shared RAM/D7: K16.19, L14.9, L15.9
/Shared RAM/D8: L16.11, M14.2, M15.2
/Shared RAM/D9: L16.12, M14.3, M15.3
/Shared RAM/D10: L16.13, M14.4, M15.4
/Shared RAM/D11: L16.15, M14.5, M15.5
/Shared RAM/D12: L16.16, M14.6, M15.6
/Shared RAM/D13: L16.17, M14.7, M15.7
/Shared RAM/D14: L16.18, M14.8, M15.8
/Shared RAM/D15: L16.19, M14.9, M15.9
/Shared RAM/~MSHLRD: F21.2, J19.14
/Shared RAM/~MSHLWR: F21.1, F26.6, J19.5
/Shared RAM/~MSHRAMEN: D24.9, F24.5, F24.10, J19.1, K17.1, L14.19, L15.19, L17.1, L18.1, M14.19, M15.19, M17.1
/Shared RAM/~MSHRAM: B23.11, E20.2, E23.1, E24.1, F24.2, F26.4, H28.14, L18.5
/Shared RAM/~MSHURD: F21.8, L18.2
/Shared RAM/~MSHUWR: E20.3, F21.9, J19.11
/Shared RAM/~SHLRD: J19.12, K16.22
/Shared RAM/~SHLWR: J19.7, K16.27
/Shared RAM/~SHRAM: K16.20, L16.20, L18.7
/Shared RAM/~SHURD: L16.22, L18.4
/Shared RAM/~SHUWR: J19.9, L16.27
/Shared RAM/~SSHLRD: D20.8, J19.13
/Shared RAM/~SSHLWR: D20.9, J17.6, J19.6
/Shared RAM/~SSHRAMEN: F24.4, F24.9, F25.13
/Shared RAM/~SSHRAM: E20.10, F24.12, H13.4, J17.5, L18.6
/Shared RAM/~SSHURD: E21.8, L18.3
/Shared RAM/~SSHUWR: E20.8, E21.9, J19.10
/Sound/SNDA4: A8.34, D9.6, D22.2, E13.4
/Sound/SNDA5: A8.35, D9.5, D22.3, E13.3
/Sound/SNDA6: A8.36, D9.4, E13.2
/Sound/SNDA7: A8.37, D9.3, E13.1
/Sound/SNDA8: A8.38, D9.25, E13.23
/Sound/SNDA9: A8.39, D9.24, E13.22
/Sound/SNDA10: A8.40, D9.21, E13.19
/Sound/SNDA11: A8.1, D9.23, E10.1
/Sound/SNDA12: A8.2, D9.2, E10.2
/Sound/SNDA13: A8.3, D9.26, E10.3
/Sound/SNDA14: A8.4, D9.27, F10.2
/Sound/SNDA15: A8.5, D9.1, F10.1
/Sound/SNDCLK: B9.4, C2.51, C11.24
/Sound/~DATARD: D22.5, F13.1
/Sound/~IORQ': E22.13, F22.13, H22.11
/Sound/~IORQ: A8.20, H22.12
/Sound/~MREQ: A8.19, E10.4
/Sound/~RAM: E10.7, E13.18, J16.9
/Sound/~RD: A8.21, C11.6, D9.22, E13.20
/Sound/~RFSH: A8.28, K11.13
/Sound/~ROM: D9.20, J16.8
/Sound/~WR: A8.22, C11.5, E13.21
/Sound/~YMCS: C11.7, D22.7
/Tile Layers/AB0: F21.5, H23.13, K19.4, L25.88, S25.66
/Tile Layers/AB1: K19.7, L25.89, N24.2, S25.67
/Tile Layers/AB2: K19.9, N24.5, S25.68
/Tile Layers/AB3: K19.12, N24.11, S25.69
/Tile Layers/AB4: M19.4, N24.14, S25.116
/Tile Layers/AB5: M19.7, N25.2, S25.115
/Tile Layers/AB6: M19.9, N25.5, S25.114
/Tile Layers/AB7: M19.12, N25.11, S25.113
/Tile Layers/AB8: M18.4, N25.14, S25.112
/Tile Layers/AB9: M18.7, N26.2, S25.111
/Tile Layers/AB10: M18.9, N26.5, S25.110
/Tile Layers/AB11: M18.12, N26.11, S25.109
/Tile Layers/AB12: L19.4, N26.14, S25.80
/Tile Layers/AB13: L19.7, N23.2, S25.81
/Tile Layers/AB14: L19.9, N23.5, S25.82
/Tile Layers/AB15: L19.12, N23.11, S25.83
/Tile Layers/COL0: N26.13, S25.37
/Tile Layers/COL2: N23.3, S25.39
/Tile Layers/COL3: N23.6, S25.40
/Tile Layers/COL4: N23.10, S25.41
/Tile Layers/COL5: L25.110, S25.42
/Tile Layers/COL6: L25.109, S25.43
/Tile Layers/COL7: L25.108, S25.46
/Tile Layers/DB0: KK22.2, L20.10, L25.79, M20.10, M21.2, S25.56
/Tile Layers/DB1: KK22.3, L20.9, L25.80, M20.9, M21.3, S25.57
/Tile Layers/DB2: KK22.4, L20.8, L25.81, M20.8, M21.4, S25.58
/Tile Layers/DB3: KK22.5, L20.7, L25.82, M20.7, M21.5, S25.59
/Tile Layers/DB4: KK22.6, L20.6, L25.83, M20.6, M21.6, S25.60
/Tile Layers/DB5: KK22.7, L20.5, L25.84, M20.5, M21.7, S25.62
/Tile Layers/DB6: KK22.8, L20.4, L25.85, M20.4, M21.8, S25.63
/Tile Layers/DB7: KK22.9, L20.3, L25.86, M20.3, M21.9, S25.64
/Tile Layers/DB8: H20.10, J20.10, K21.2, L21.2
/Tile Layers/DB9: H20.9, J20.9, K21.3, L21.3
/Tile Layers/DB10: H20.8, J20.8, K21.4, L21.4
/Tile Layers/DB11: H20.7, J20.7, K21.5, L21.5
/Tile Layers/DB12: H20.6, J20.6, K21.6, L21.6
/Tile Layers/DB13: H20.5, J20.5, K21.7, L21.7
/Tile Layers/DB14: H20.4, J20.4, K21.8, L21.8
/Tile Layers/DB15: H20.3, J20.3, K21.9, L21.9
/Tile Layers/P1H': D20.4, F21.3, N23.1, N24.1, N25.1, N26.1
/Tile Layers/RA0: N28.10, R28.10, S25.2
/Tile Layers/RA1: N28.9, R28.9, S25.120
/Tile Layers/RA2: N28.8, R28.8, S25.119
/Tile Layers/RA3: N28.7, R28.7, S25.118
/Tile Layers/RA4: N28.6, R28.6, S25.117
/Tile Layers/RA5: N28.5, R28.5, S25.70
/Tile Layers/RA6: N28.4, R28.4, S25.71
/Tile Layers/RA7: N28.3, R28.3, S25.72
/Tile Layers/RA8: N28.25, R28.25, S25.73
/Tile Layers/RA9: N28.24, R28.24, S25.76
/Tile Layers/RA10: N28.21, R28.21, S25.77
/Tile Layers/RA11: N28.23, R28.23, S25.78
/Tile Layers/RA12: N28.2, R28.2, S25.79
/Tile Layers/VC0: L25.29, M21.11, M23.19
/Tile Layers/VC1: L25.28, M21.15, M23.15
/Tile Layers/VC2: K21.11, L25.27, M28.19
/Tile Layers/VC3: K21.15, L25.26, M28.15
/Tile Layers/VC4: KK22.11, L25.25, M26.19
/Tile Layers/VC5: KK22.15, L25.24, M26.15
/Tile Layers/VC6: L21.11, L25.23, M24.19
/Tile Layers/VC7: L21.15, L25.22, M24.15
/Tile Layers/VC8: L25.21, M21.12, M23.18
/Tile Layers/VC9: L25.20, M21.16, M23.13
/Tile Layers/VC10: K21.12, L25.19, M28.18
/Tile Layers/VC11: K21.16, L25.18, M28.13
/Tile Layers/VC12: KK22.12, L25.17, M26.18
/Tile Layers/VC13: KK22.16, L25.16, M26.13
/Tile Layers/VC14: L21.12, L25.13, M24.18
/Tile Layers/VC15: L21.16, L25.12, M24.13
/Tile Layers/VC16: L25.11, M21.13, M23.17
/Tile Layers/VC17: L25.10, M21.17, M23.12
/Tile Layers/VC18: K21.13, L25.9, M28.17
/Tile Layers/VC19: K21.17, L25.8, M28.12
/Tile Layers/VC20: KK22.13, L25.7, M26.17
/Tile Layers/VC21: KK22.17, L25.6, M26.12
/Tile Layers/VC22: L21.13, L25.5, M24.17
/Tile Layers/VC23: L21.17, L25.4, M24.12
/Tile Layers/VC24: L25.3, M21.14, M23.16
/Tile Layers/VC25: L25.2, M21.18, M23.11
/Tile Layers/VC26: K21.14, L25.120, M28.16
/Tile Layers/VC27: K21.18, L25.119, M28.11
/Tile Layers/VC28: KK22.14, L25.118, M26.16
/Tile Layers/VC29: KK22.18, L25.117, M26.11
/Tile Layers/VC30: L21.14, L25.116, M24.16
/Tile Layers/VC31: L21.18, L25.115, M24.11
/Tile Layers/VCA0: N24.3, S25.35
/Tile Layers/VCA1: N24.6, S25.34
/Tile Layers/VCA2: N24.10, S25.33
/Tile Layers/VCA3: N24.13, S25.32
/Tile Layers/VCA4: N25.3, S25.30
/Tile Layers/VCA5: N25.6, S25.29
/Tile Layers/VCA6: N25.10, S25.28
/Tile Layers/VCA7: N25.13, S25.27
/Tile Layers/VCA8: N26.3, S25.26
/Tile Layers/VCA9: N26.6, S25.25
/Tile Layers/VCA10: N26.10, S25.24
/Tile Layers/VCA'0: M23.10, M24.10, M26.10, M28.10, N23.4
/Tile Layers/VCA'1: M23.9, M24.9, M26.9, M28.9, N23.7
/Tile Layers/VCA'2: M23.8, M24.8, M26.8, M28.8, N23.9
/Tile Layers/VCA'3: M23.7, M24.7, M26.7, M28.7, N23.12
/Tile Layers/VCA'4: M23.6, M24.6, M26.6, M28.6, N26.4
/Tile Layers/VCA'5: M23.5, M24.5, M26.5, M28.5, N26.7
/Tile Layers/VCA'6: M23.4, M24.4, M26.4, M28.4, N26.9
/Tile Layers/VCA'7: M23.3, M24.3, M26.3, M28.3, N26.12
/Tile Layers/VCA'8: M23.25, M24.25, M26.25, M28.25, N25.4
/Tile Layers/VCA'9: M23.24, M24.24, M26.24, M28.24, N25.7
/Tile Layers/VCA'10: M23.21, M24.21, M26.21, M28.21, N25.9
/Tile Layers/VCA'11: M23.23, M24.23, M26.23, M28.23, N25.12
/Tile Layers/VCA'12: M23.2, M24.2, M26.2, M28.2, N24.4
/Tile Layers/VCA'13: M23.26, M24.26, M26.26, M28.26, N24.7
/Tile Layers/VCA'14: M23.1, M24.1, M26.1, M28.1, N24.9
/Tile Layers/VD0: N28.11, S25.20
/Tile Layers/VD1: N28.12, S25.19
/Tile Layers/VD2: N28.13, S25.18
/Tile Layers/VD3: N28.15, S25.17
/Tile Layers/VD4: N28.16, S25.16
/Tile Layers/VD5: N28.17, S25.13
/Tile Layers/VD6: N28.18, S25.12
/Tile Layers/VD7: N28.19, S25.11
/Tile Layers/VD8: R28.11, S25.10
/Tile Layers/VD9: R28.12, S25.9
/Tile Layers/VD10: R28.13, S25.8
/Tile Layers/VD11: R28.15, S25.7
/Tile Layers/VD12: R28.16, S25.6
/Tile Layers/VD13: R28.17, S25.5
/Tile Layers/VD14: R28.18, S25.4
/Tile Layers/VD15: R28.19, S25.3
/Tile Layers/~CHRAMOE1: H23.12, J23.9, J23.12, K21.19, M21.19
/Tile Layers/~CHRAMOE2: H23.6, J23.3, J23.6, KK22.19, L21.19
/Tile Layers/~CHRAMWE1: M23.27, N22.11
/Tile Layers/~CHRAMWE2: M28.27, N22.3
/Tile Layers/~CHRAMWE3: M24.27, N22.6
/Tile Layers/~CHRAMWE4: M26.27, N22.8
/Tile Layers/~CHRAMWE: N22.1, N22.4, N22.9, N22.12, S25.89
/Tile Layers/~CLK6M: D23.11, H25.6, J18.11
/Tile Layers/~P1H'': F21.4, H23.2, H23.4
/Tile Layers/~P1H': D20.3, D20.12, E22.3, H20.12, J20.12, K12.11, L20.12, M20.12
/Tile Layers/~TILERAMCS: H22.6, L25.97, S25.54, S25.84
/Tile Layers/~TILEREAD: K21.1, KK22.1, L21.1, L25.87, M21.1, S25.85, U1.9
/Tile Layers/~VRAMCS1: R28.20, S25.93
/Tile Layers/~VRAMOE1: R28.22, S25.95
/Tile Layers/~VRAMOE2: N28.22, S25.96
/Tile Layers/~VRAMWE1: R28.27, S25.107
/Tile Layers/~VRAMWE2: N28.27, S25.108
/Tile Logic/~LWR: J23.5, J23.8, U1.4
/Tile Logic/~MCPUEN': D23.12, E22.5, F20.13, F23.10
/Tile Logic/~MCPUEN: E22.2, F22.4, F22.9, F23.4, F26.10
/Tile Logic/~MVRAMCS: B23.10, F23.9, H22.2
/Tile Logic/~SCPUEN': J17.2, J17.13, J18.12, K12.9
/Tile Logic/~SCPUEN: F20.9, F22.5, F22.10, J17.10, K12.12, K19.1, L19.1, M18.1, M19.1, U1.1
/Tile Logic/~SVRAMCS: H13.5, J13.2, J17.12
/Tile Logic/~UWR: J23.2, J23.11, U1.7
/~CLK24M: F22.3, F24.11, H25.12
/~SYSRES: A8.26, B11.7, C2.63, C11.3, C21.1, D4.119, D21.1, D23.1, E25.1, F25.9, F25.11, H22.10, H22.13, J18.5, L25.92, R7.119, S25.55
GND: A1.3, A1.7, A3.1, A8.29, A24.1, A24.19, B3.1, B10.11, B11.3, B11.8, B11.16, B12.13, B12.14, B15.1, B15.11, B15.30, B18.1, B18.11, B18.30, B21.15, B22.4, C2.16, C2.48, C9.11, C11.1, C11.11, C14.16, C16.16, C18.16, C20.16, D4.1, D4.9, D4.15, D4.23, D4.31, D4.45, D4.61, D4.75, D4.83, D4.91, D4.99, D4.105, D4.118, D9.14, D22.15, D26.12, D26.18, D27.12, D27.18, E6.16, E8.16, E13.12, E15.16, E15.22, E16.14, E19.16, E19.53, F15.16, F15.22, F16.14, F27.15, F28.15, H3.10, H3.11, H3.30, H6.16, H8.16, H13.15, H20.11, H21.2, H21.12, H28.13, H28.15, J14.1, J14.19, J15.1, J19.15, J20.11, J22.2, J22.12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
unnamed: A8.6, B9.2
unnamed: A8.16, E22.8
unnamed: B10.1, B10.2
unnamed: B10.6, B10.7
unnamed: B10.10, B11.12
unnamed: B10.8, B10.9
unnamed: B10.12, B11.15
unnamed: B10.13, B11.14
unnamed: B11.9, C9.5
unnamed: B11.10, C9.3
unnamed: B10.14, B11.13
unnamed: B11.6, C11.20
unnamed: B11.5, C11.19
unnamed: B11.4, C11.21
unnamed: B11.2, C11.23
unnamed: B21.2, D21.2
unnamed: B21.5, D21.5
unnamed: B21.3, D21.7
unnamed: B21.6, D21.10
unnamed: B21.4, C21.3
unnamed: B21.7, C21.4
unnamed: B22.5, B23.12
unnamed: B22.15, E25.11
unnamed: B23.13, E21.1
unnamed: B9.8, C2.58
unnamed: B3.2, C2.17
unnamed: B3.3, C2.18
unnamed: B3.4, C2.19
unnamed: B3.5, C2.20
unnamed: B3.6, C2.21
unnamed: B3.7, C2.22
unnamed: B3.8, C2.23
unnamed: A3.2, C2.9
unnamed: A3.3, C2.10
unnamed: A3.4, C2.11
unnamed: A3.5, C2.12
unnamed: A3.6, C2.13
unnamed: A3.7, C2.14
unnamed: A3.8, C2.15
unnamed: C2.53, D7.11
unnamed: B9.5, C2.55
unnamed: C9.1, C9.2
unnamed: C9.6, C9.7
unnamed: C25.14, C26.14, D28.14, E28.14, H25.2
unnamed: C25.2, C26.2, D28.2, E28.2, H25.4
unnamed: D22.1, E10.9, J16.10
unnamed: D23.9, D24.13
unnamed: D23.10, E22.4, H22.8
unnamed: D24.11, F23.3
unnamed: D26.21, F26.3
unnamed: D27.21, F26.11
unnamed: E10.5, K11.12
unnamed: E10.6, F10.3
unnamed: E19.25, J22.5
unnamed: E19.24, H21.9
unnamed: E19.23, H21.5
unnamed: E19.21, J16.3
unnamed: E21.2, E21.3
unnamed: E21.10, F23.13
unnamed: F20.2, F21.12
unnamed: F20.3, F20.4
unnamed: F20.11, J16.13
unnamed: F21.6, H23.5
unnamed: F22.2, J13.3
unnamed: F22.12, H22.3
unnamed: F23.8, H22.4
unnamed: F23.11, H24.1
unnamed: B9.1, B9.3
unnamed: H13.1, H24.3
unnamed: H13.7, K12.2
unnamed: F26.8, H20.21, L20.21
unnamed: F23.6, H20.2, L20.2
unnamed: H21.11, K11.2
unnamed: H22.5, J17.11
unnamed: H23.1, H23.3, J16.11
unnamed: H26.10, H26.13
unnamed: J14.8, J14.13, J14.17
unnamed: J13.9, K13.11
unnamed: F23.1, J15.16
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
